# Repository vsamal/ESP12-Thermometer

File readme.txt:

Eagle library
https://library.io/libraries/16909046-Ipfcz

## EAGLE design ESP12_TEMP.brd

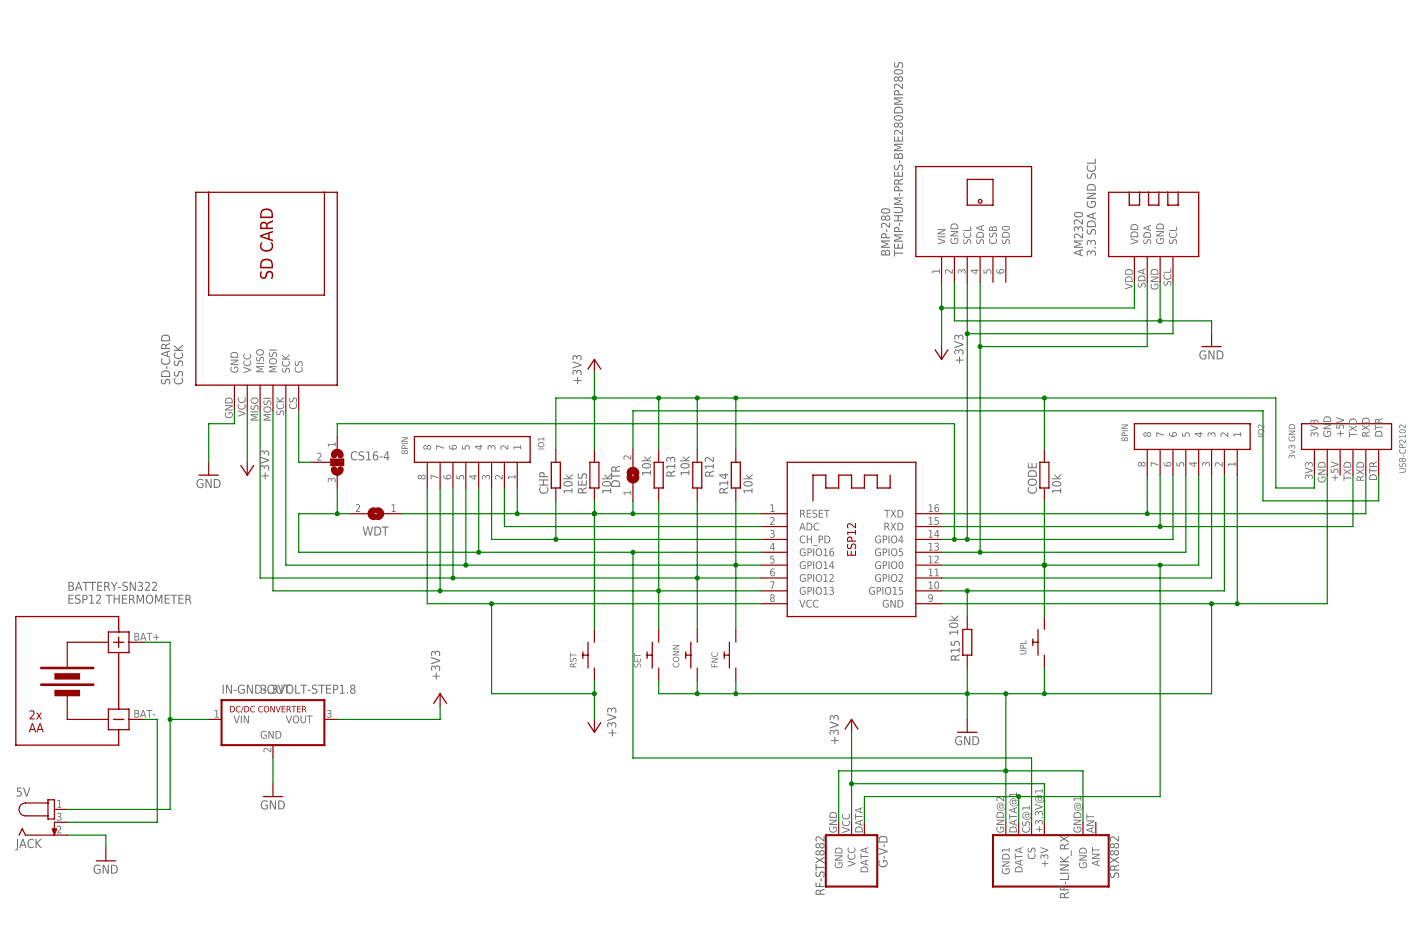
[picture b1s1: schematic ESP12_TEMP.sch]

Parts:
5V: JACK
AM2320: 3.3 SDA GND SCL; TEMP-HUM-SENSOR-AM2322S
BATTERY-SN322: ESP12 THERMOMETER; BATTERY-HOLDER-2AA
BMP-280: TEMP-HUM-PRES-BME280DMP280S; TEMP-HUM-PRES-BME280S
CHP: 10k; 0204/5
CODE: 10k; 0204/5
CONN: SWITCH_PUSHBUTTONEVQ-PE; TACT_PANA-EVQ
CS16-4: JUMERS3-SMD; SJ_2
DTR: JUMPER-SMD; SJ
ESP12E: ESP-12
FNC: SWITCH_PUSHBUTTONEVQ-PE; TACT_PANA-EVQ
G-V-D: RF-STX882; RF-LINK_TX
IN-GND-OUT: 3.3VOLT-STEP1.8; SIP3
IO1, IO2: 8PIN
R12, R13, R14, R15: 10k; 0204/5
RES: 10k; 0204/5
RST: SWITCH_PUSHBUTTONEVQ-PE; TACT_PANA-EVQ
SD-CARD: CS SCK; CARD-SD-ADAPTERS
SET: SWITCH_PUSHBUTTONEVQ-PE; TACT_PANA-EVQ
SRX882: RF-LINK_RX
UPL: SWITCH_PUSHBUTTONEVQ-PE; TACT_PANA-EVQ
USB-CP2102: 3v3 GND; USB-UART
WDT: JUMPER-SMD; SJ

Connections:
+3V3: AM2320.VDD, BMP-280.1 (VIN), CHP.2, CODE.2, ESP12E.8 (VCC), G-V-D.VCC, IN-GND-OUT.3 (VOUT), IO1.8, R12.1, R13.1, R14.2, RES.2, RST.P$1, SD-CARD.VCC, SRX882.+3.3V@1 (+3V), USB-CP2102.3V3
+5V: USB-CP2102.+5V
BAT$1: 5V.1, BATTERY-SN322.BAT+, IN-GND-OUT.1 (VIN)
BAT$2: 5V.3, BATTERY-SN322.BAT-
GND: 5V.2, AM2320.GND, BMP-280.2 (GND), CONN.P$1, ESP12E.9 (GND), FNC.P$1, G-V-D.GND, IN-GND-OUT.2 (GND), IO2.1, R15.1, SD-CARD.GND, SET.P$1, SRX882.GND@1 (GND), SRX882.GND@2 (GND1), UPL.P$1, USB-CP2102.GND
unnamed: DTR.2, USB-CP2102.DTR
unnamed: DTR.1, ESP12E.1 (RESET), IO1.1, RES.1, RST.P$2, WDT.1
unnamed: ESP12E.2 (ADC), IO1.2
unnamed: CHP.1, ESP12E.3 (CH_PD), IO1.3
unnamed: CS16-4.3, ESP12E.4 (GPIO16), IO1.4, SRX882.CS@1 (CS), WDT.2
unnamed: ESP12E.5 (GPIO14), FNC.P$2, IO1.5, R14.1, SD-CARD.SCK
unnamed: CONN.P$2, ESP12E.6 (GPIO12), IO1.6, R12.2, SD-CARD.MISO
unnamed: ESP12E.7 (GPIO13), IO1.7, R13.2, SD-CARD.MOSI, SET.P$2
unnamed: CS16-4.2, SD-CARD.CS
unnamed: ESP12E.16 (TXD), IO2.8, USB-CP2102.RXD
unnamed: ESP12E.15 (RXD), IO2.7, USB-CP2102.TXD
unnamed: AM2320.SCL, BMP-280.3 (SCL), CS16-4.1, ESP12E.14 (GPIO4), IO2.6
unnamed: CODE.1, ESP12E.12 (GPIO0), G-V-D.DATA, IO2.4, SRX882.DATA@1 (DATA), UPL.P$2
unnamed: ESP12E.11 (GPIO2), IO2.3
unnamed: ESP12E.10 (GPIO15), IO2.2, R15.2
unnamed: AM2320.SDA, BMP-280.4 (SDA), ESP12E.13 (GPIO5), IO2.5

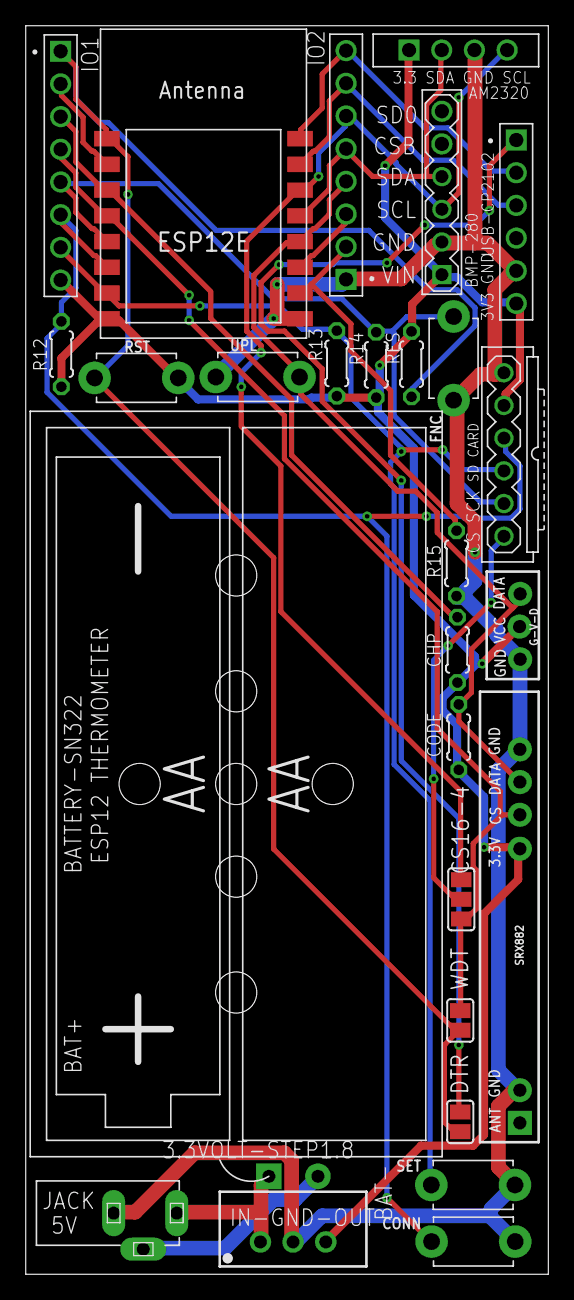
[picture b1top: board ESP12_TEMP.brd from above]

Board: 2 copper layers, 40.6 x 97.0 mm, 27 parts (0 on the bottom side), 20 nets.

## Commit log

2020-02-09 Upload Files
